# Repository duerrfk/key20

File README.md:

# What is Key 2.0?

Key 2.0 (or Key20 for short) is a Bluetooth IoT Door Lock controller. It turns a conventional electric door lock into a smart door lock that can be opened using a smartphone without the need for a physical key. Thus, Key20 is the modern version of a physical key, or, as the name suggests, the key version 2.0 for the Internet of Things (IoT) era.

Key20 consists of two parts:

1. Key20 door lock controller device, which is physically connected to the electric door lock and wirelessly via BLE to the mobile app.
2. Key20 mobile app implementing the user interface to unlock the door and communicating with the door lock controller through BLE.

```
         [ Mobile Phone w/ ]
         [    Key20 App    ]
               |
               | Bluetooth Low Energy (BLE) Connection
               |
 |---[ Key20 Door Lock Controller ]---[ Electric Door Lock ]---|
 |   [           Device           ]                            |
 |                                                             |
 |                                                             |
 |                                                             |
 |----------------------(Voltage Source)-----------------------|
                        (    12 VAC    )
```

The following image shows the Key20 door lock controller device and the Key20 app running on a smartphone.

You can get a quick impression on how Key20 works watching the following video:

[Key 2.0 Video](https://youtu.be/0vUUZOasrV8)

The main features of Key20 are:

* Using state-of-the-art security mechanisms (Elliptic Curve Diffie-Hellman Key Exchange (ECDH), HMAC) to protect against attacks. 
* Open-source software and hardware, including an open implementation of the security mechanisms. No security by obscurity! Source code for the app and door lock controller as well as Eagle files (schematic and board layout) are provided.
* Maker-friendly: using easily available cheap standard components (nRF51822 BLE chip, standard electronic parts), easy to manufacture circuit board, and open-source software and hardware design.
* Works with BLE-enabled Android 4.3 mobile devices (and of course newer versions). Porting to other mobile operating systems like iOS should be straightforward.
* Liberal licensing of software and hardware under the Apache License 2.0 and the CERN Open Hardware License 1.0, respectively.

# Security Concepts

A door lock obviously requires security mechanisms to protect from unauthorized requests to open the door. To this end, Key20 implements the following state of the art security mechanisms.

## Authorization of Door Open Requests with HMAC

All door open requests are authorized through a Keyed Hash Message Authentication Code (HMAC). A 16 byte nonce (big random number) is generated by the door lock controller for each door open request as soon as a BLE connection is made to the door lock controller. The nonce is sent to the mobile app. Both, the nonce and the shared secret, are used by the mobile app to calculate a 512 bit HMAC using the SHA-2 hashing algorithm, which is then truncated to 256 bits (HMAC512-256), and sent to the door lock controller. The door lock controller also calculates an HMAC based on the nonce and the shared secret, and only if both HMACs match, the door will be opened. 

The nonce is only valid for one door open request and effectively prevents replay attacks, i.e., an attacker sniffing on the radio channel and replaying the sniffed HMAC later. Note that the BLE radio communication is not encrypted, and it actually does not need to be encrypted since a captured HMAC is useless when re-played. 

Moreover, each nonce is only valid for 15 s to prevent man-in-the-middle attacks where an attacker intercepts the HMAC and does not forward it immediatelly but waits until the (authorized) user walks away after he is not able to open the door. Later the attacker would then send the HMAC to the door lock controller to open the door. With a time window of only 15 s (which could be reduced further), such attacks are futile since the authorized user will still be at the door.

Note that the whole authentication procedure does not include heavy-weight asymmetric crypto functions, but only light-weight hashing algorithms, which can be performed on the door lock device featuring an nRF51822 micro-controller (ARM Cortex M0) very fast in order not to delay door unlocking. 

With respect to the random nonce we would like to note the following. First, the nRF51822 chip includes a random number generator for generating random numbers from thermal noise, so nonces should be of high quality, i.e., truly random. An attack by cooling down the Bluetooth chip to reduce randomness due to thermal noise is not relevant here since this requires physical access to the lock controller installed within the building, i.e., the attacker is then already in your house.

Secondly, 128 bit nonces provide reasonable security for our purpose. Assume one door open request per millisecond (very pessimistic assumption!) and 100 years of operation, i.e., less than n = 2^42 requests to be protected. With 128 bit nonces, we have m = 2^128 possible nonce values. Then the birthday paradox can be used to calculate the probability p of at least one pair of requests sharing the same nonce, or, inversely, no nonces shared by any pair of requests. An approximation of p for n << m is p(n,m) = 1 - e^((-n^2)/(2*m)), which practically evaluates to 0 for n = 2^42 and m = 2^128. Even for n = 2^52 (one request per us; actually not possible with BLE), p(2^52,2^128) < 3e-8, which is about the probability to be hit by lightning, which is about 5.5e-8.

## Exchanging Keys with Elliptic Curve Diffie Hellman Key Exchange (ECDH)

Obviously, the critical part is the establishment of a shared secret between the door lock controller and the mobile app. Anybody in possession of the shared secret can enter the building, thus, we must ensure that only the lock controller and the Key20 app know the secret. To this end, we use Elliptic Curve Diffie-Hellman (ECDH) key exchange based on Curve 25519. We assume that the door lock controller is installed inside the building that is secured by the lock---if the attacker is already in your home, the door lock is futile anyway. Thus, only the authorized user (owner of the building) has physical access to the door lock controller. 

First, the user needs to press a button on the door lock controller device to enter key exchange mode (the red button in the pictures). Then both, the mobile app and the door lock controller calculate different key pairs based on the Elliptic Curve 25519 and exchange their public keys, which anyone can know. Using the public key of the other party and their own private keys, the lock controller and the app can calculate the same shared secret. 

Using Curve 25519 and the Curve 25519 assembler implementation optimized for ARM Cortex-M0 from the Micro NaCl project, key pairs and shared secrets can be calculated in sub-seconds on the nRF51822 BLE chip (ARM Cortex M0). 

Without further measures, DH is susceptible to man-in-the-middle attacks where an attacker actively manipulates the communication between mobile app and door lock controller. With such attacks, the attacker could exchange his own public key with both, the lock controller and the app to establish two shared secrets between him and the door lock controller, and between him and the mobile app. We prevent such attacks with the following mechanism. After key exchange, the mobile app and the door lock device both display a checksum (hash) of their version of the exchanged shared secret. The user will visually check these checksums to verify that they are the same. If they are the same, no man-in-the-middle attack has happened since the man in the middle cannot calculate the same shared secret as the door lock controller and the mobile app (after all, the private keys of door lock controller and mobile app remain private). Only then the user will confirm the key by pressing buttons on the door lock controller and the mobile app. Remember that only the authorized user has physical access to the door lock controller since it is installed within the building to be secured by the lock. 

The following image shows the mobile app and the door lock controller displaying a shared secret checksum after key exchange. The user can confirm this secret by pushing the green button the the lock controller device and the Confirm Key button of the app.

## Why not Standard Bluetooth Security?

Actually, Bluetooth 4.2 implements security concepts similar to the mechanisms described above. So it is a valid question why don't we just rely on the security concepts implemented by Bluetooth?

A good overview why Bluetooth might not be as secure as we would like it to be is provided by [Francisco Corella](https://pomcor.com/2015/06/03/has-bluetooth-become-secure/). So we refer the interested reader to his page for the technical details and a discussion of Bluetooth security. We also would like to add that many mobile devices still do not implement Bluetooth 4.2 but only Bluetooth 4.0, which is even less secure than Bluetooth 4.2.

So we decided not to rely on Bluetooth security mechanisms, but rather implement all security protocols on the application layer using state of the art security mechanisms as described above.

# Bluetooth Door Lock Controller Device

The Door Lock Controller Device needs to be connected to the electric door lock (2 cables). You can simply replace a manual switch by the door lock controller device. 

The door lock controller needs to be placed in Bluetooth radio range to the door and inside the building. Typical radio ranges are about 10 m. Depending on the walls, the distance might be shorter or longer. In our experience, one concrete wall is no problem, but two might block the radio signal.  

## Door Lock Controller Hardware

The door lock controller hardware is designed for operating AC (alternating current) electric door locks, which typically run from 6-12 VAC. 

The hardware design (schematics and board layout for Eagle) for the door lock controller device can be found in folder `pcb/key20-ble`. 

The following images show the hardware and schematic. The hardware basically concists of one circuit board (PCB). We deliberately used a simple single-sided through-hole design to help makers producing their own boards. An LCD, a power switch, and two push buttons for user interaction are connected to the main PCB. An ob-board voltage regulator provides 3.3 V fed by an external DC power supply (anything between 4 V and 30 V will work). The circuit draws less than 50 mA when the lock is operated, thus, you can use a cheap 5.0 V USB power supply. With a little modification, we could also switch off the LCD when not needed, and the device could run from 4 AA-size batteries most probably for years.

The main part of the hardware is an nRF51822 BLE chip from Nordic Semiconductors. You can buy so-called "Bluetooth 4.0" breakout boards with an nRF51822 (version 3, variant AA w/ 16 kB of RAM and 256 kB flash memory) and two 2x9 connectors (2 mm pitch) for about 6 US$ including shipping. To connect the Bluetooth 4.0 board hosting the nRF51822, the PCB has two 2x9 pin connectors (no SMD soldering required). The nRF51822 features an ARM Cortex M0 micro-controller and a so-called softdevice implementing the Bluetooth stack, which runs together with the application logic on the ARM Cortex M0 processor. Key20 uses the S110 softdevice version 8.0 (see next sub-section on how to flash the softdevice and the Key20 application code). 

The nRF51822 operates the electric door lock through a TRIAC. Note that most electric door locks use alternating current (AC), so a transistor will not work. We have added a snubber circuit (capacitor and resistor) to drive the inductive load (electric door lock) since TRIACs are sensitive to sudden voltage jumps possibly leading to unwanted turn-on, i.e., door unlocking. The TRIAC is operated in quadrant 2 and 3 (current flowing out of the gate) to avoid the less sensitive quadrant 4. Since the TRIAC needs about 30 mA to trigger reliably, a transistor is used to drive the TRIAC by the nRF51822, reducing the current on the micro-controller's GPIO to less than 1 mA.

Note that our design is targeting electric door locks using small AC voltages (typically 6-12 V AC). Theoretically, the TRIAC can drive 230 V loads up to 16 A. However, for safe 230 V and higer current operation the design has to be adapted, e.g., X2 snubber capacitor, isolation of the low-voltage part (3.3 V microcontroller) from the 230 V part through an opto-TRIAC, larger trace width and distances, etc. 

An LCD is used to implement the secure key exchange procedure described above (visual key verification to avoid man-in-the-middle attacks). We used a common HD44780-compatible LCD display with 2x16 characters (1602A, 2-3 US$ including shipping). The LCD is connected to the main PCB through a ribbon cable. We designed a custom adapter board for connecting and mounting the 1602A LCD (see folder `pcb/lcd1602a-connector`).

## Lock Controller Software

### Overview

The software for the door lock controller can be found in folder `nrf51`.

Keys (shared secrets) are persistently stored in flash. Currently, we store 4 keys, but you can easily increase this number up to the limit of the flash size (nRF51822 version 3, variant AA comes with 256 kB flash, and each key consumes only 32 bytes).  

Application events and a state machine approach are used to implement the application logic. Events are handled outside the interrupt context to avoid blocking the softdevice. In particular, actions like calculating keys or hashes can take significant time, although the crypto implementations used by Key20 can also process such compute-heavy tasks in just hundreds of milliseconds.   

A lean-and-mean library was implemented for the nRF51822 chip to drive the LCD. 

For more details, please have a look at the source code.

### Prerequisites for Building the Software

No heavy-weight IDE is required to build the code. However, still a few tools are required to build and flash the code (tested with the given version numbers):

* [nRF51 SDK, version 10.0.0](http://developer.nordicsemi.com/nRF5_SDK/)
* [nRF5x Command Line Tools, version 8.2.0](https://www.nordicsemi.com/eng/Products/nRF51-DK)
* [Softdevice S110, version 8.0.0](https://www.nordicsemi.com/eng/Products/nRF51-DK)
* Flashing and debugging hardware, e.g., [Segger J-Link EDU](https://www.segger.com/j-link-edu.html) (about 50 US$, only for non-commerical use!). The nRF51 Developers Kit (DK) comes with an on-board Segger programmer, but for flashing the Key20 board, you need an external programmer like the J-Link EDU. 
* [Tool chain (compiler, linker, etc.) for ARM](https://launchpad.net/gcc-arm-embedded/+download)

### Building and Flashing the Software

First, adapt the Makefile by defining the following variables:

* `NRF51_SDK`: path to the nRF51 SDK directory
* `CROSS`: path to the compiler tools
* `CFLAGS`: add `-DTARGET_BOARD_NRF51DK` if you compile for the nRF51 Development Kit (DK); if this definition is not set, you compile for the Key20 board.
* `LINKER_SCRIPT`: set to `nrf51422_ac_s110.ld` for the nRF51 DK (nRF51422, variant AC) or to `nrf51822_aa_s110.ld` for the Key20 board (nRF51822, variant AA).

Compiling the code:

```
$ cd nrf51
$ make
```

Flashing the softdevice:

```
$ nrfjprog --family NRF51 --program s110_nrf51_8.0.0_softdevice.hex --chiperase --verify
```

Flashing the application:

```
nrfjprog --family NRF51 --program key20.hex --verify --sectorerase
```

Rebooting after flashing:

```
nrfjprog -r
```

# Android App

The source code of the Key20 app for Android can be found in folder `android/Key20`. The code was developed with Android Studio 2.1.

The app requires a BLE-enabled mobile device running Android version 4.3 "Jelly Bean" (API level 18) or higher. 

The following images show the two major tabs of the app: one for opening the door, and the second for exchanging keys between the app and the door lock controller.

# License and Acknowledgments

The Key20 software (contents of folders `nrf51` and `android`) is licensed under the Apache License, Version 2.0.

The Key20 hardware documentation (contents of folder `pcb`) is licensed under the CERN Open Hardware Licence, Version 1.2

Both licenses are included in the repository in the files `LICENSE-SOFTWARE` and `LICENSE-HARDWARE`, respectively.

Key20 uses the Micro-NaCl crypto library, specifically, AVRNaCl (folder `avrnacl`) by Michael Hutter and Peter Schwabe, and M0NaCl  (folder `curve25519-cortexm0`) by Björn Haase and Ana Helena Sánchez. The authors have released Micro-NaCl to the public domain, and we gratefully acknowledge their generous contribution.

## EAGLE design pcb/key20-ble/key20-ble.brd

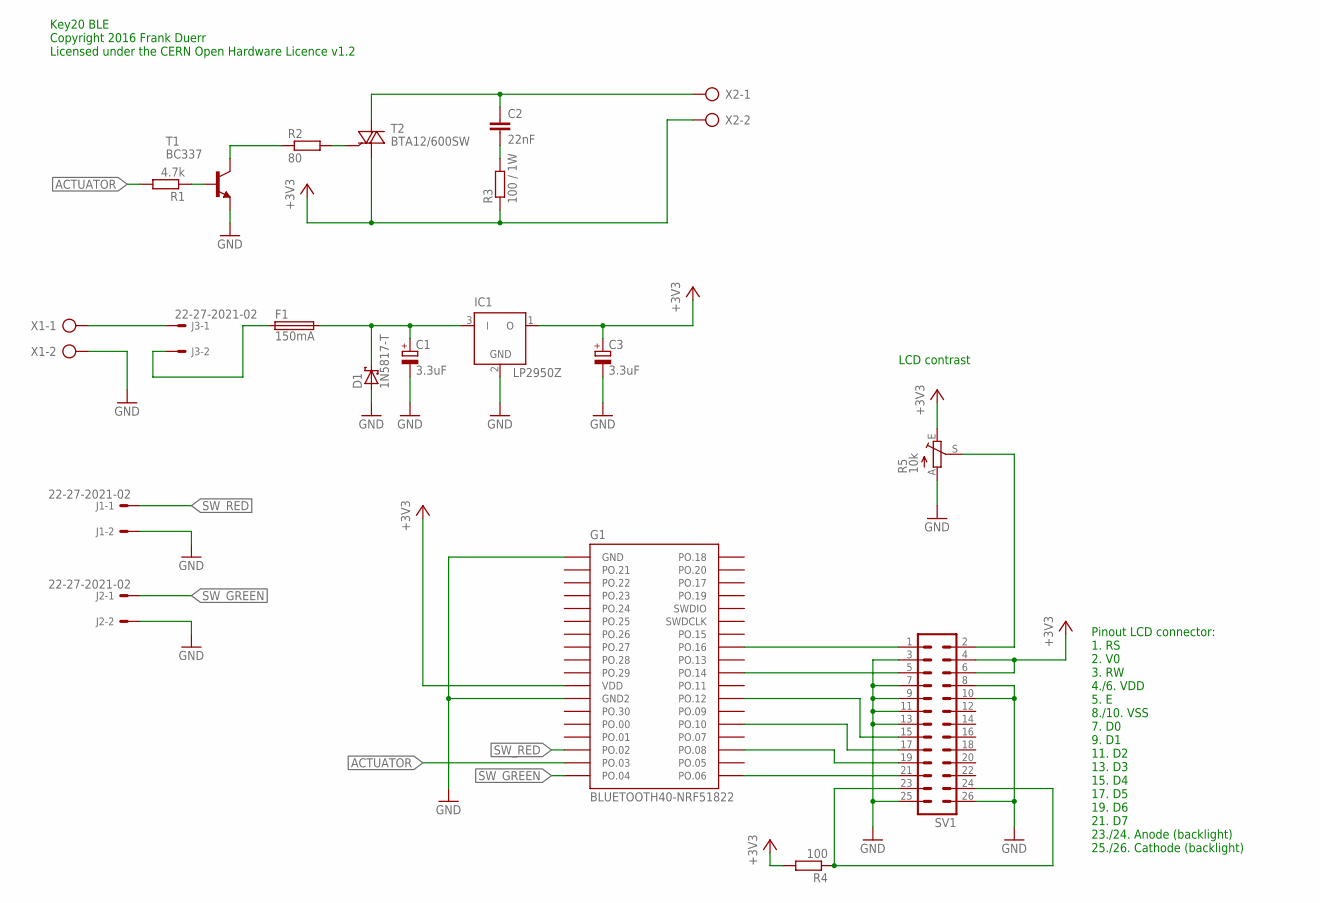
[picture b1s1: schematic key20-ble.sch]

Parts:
C1, C3: 3.3uF; E2,5-5
C2: 22nF; C102-054X133
D1: 1N5817-T; DO41-7.6
F1: 150mA; SH22,5
G1: BLUETOOTH40-NRF51822; BLUETOOTH40-NR51822
IC1: LP2950Z; TO92
J1, J2, J3: 22-27-2021-02; 6410-02
R1: 4.7k; 0207/7
R2: 80; 0207/7
R3: 100 / 1W; 0207/7
R4: 100; 0207/7
R5: 10k; CA6V
SV1: ML26
T1: BC337; TO92
T2: BTA12/600SW; TO220BV
X1, X2: AK500/2

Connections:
+3V3: C3.+, G1.VDD, IC1.1 (O), R3.1, R4.2, R5.E, SV1.4, SV1.6, T2.T1 (A1), X2.2
ACTUATOR: G1.PO.03, R1.2
GND: C1.-, C3.-, D1.A, G1.GND, G1.GND2, IC1.2 (GND), J1.2, J2.2, R5.A, SV1.3, SV1.7, SV1.8, SV1.9, SV1.10, SV1.11, SV1.13, SV1.25, SV1.26, T1.1 (E), X1.2
unnamed: R2.2, T2.G
unnamed: C2.2, R3.2
unnamed: C2.1, T2.T2 (A2), X2.1
unnamed: R1.1, T1.2 (B)
unnamed: R2.1, T1.3 (C)
unnamed: G1.PO.08, SV1.19
unnamed: F1.1, J3.2
unnamed: G1.PO.06, SV1.21
unnamed: G1.PO.14, SV1.5
unnamed: G1.PO.16, SV1.1
unnamed: R5.S, SV1.2
unnamed: R4.1, SV1.23, SV1.24
unnamed: J3.1, X1.1
unnamed: C1.+, D1.C, F1.2, IC1.3 (I)
unnamed: G1.PO.10, SV1.17
unnamed: G1.PO.12, SV1.15
SW_GREEN: G1.PO.04, J2.1
SW_RED: G1.PO.02, J1.1

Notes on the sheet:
Pinout LCD connector: 1. RS 2. V0 3. RW 4./6. VDD 5. E 8./10. VSS 7. D0 9. D1 11. D2 13. D3 15. D4 17. D5 19. D6 21. D7 23./24. Anode (backlight) 25./26. Cathode (backlight)
LCD contrast
Key20 BLE Copyright 2016 Frank Duerr Licensed under the CERN Open Hardware Licence v1.2

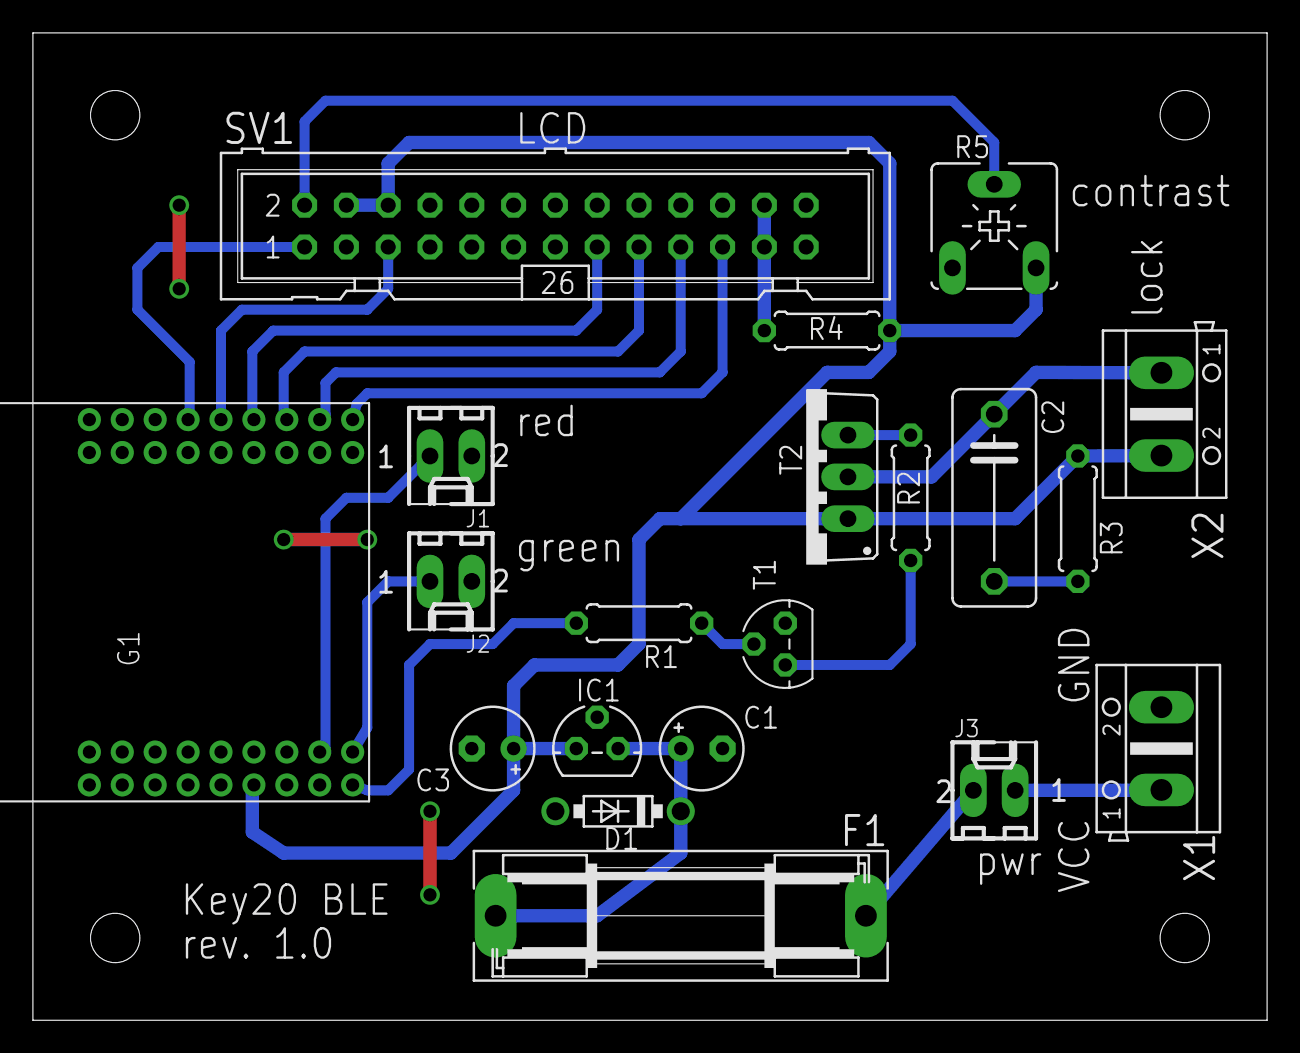
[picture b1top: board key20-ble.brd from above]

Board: 2 copper layers, 75.0 x 60.0 mm, 20 parts (0 on the bottom side), 21 nets.

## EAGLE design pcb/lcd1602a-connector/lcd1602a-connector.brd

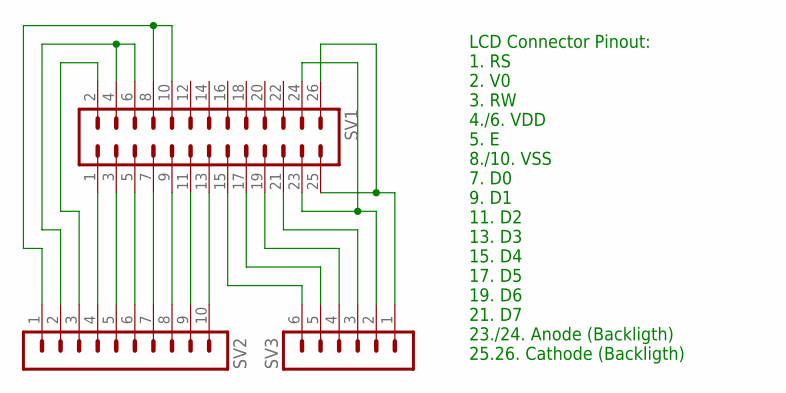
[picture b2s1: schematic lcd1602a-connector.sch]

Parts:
SV1: ML26
SV2: MA10-1
SV3: MA06-1

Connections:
unnamed: SV1.1, SV2.4
unnamed: SV1.3, SV2.5
unnamed: SV1.5, SV2.6
unnamed: SV1.7, SV2.7
unnamed: SV1.9, SV2.8
unnamed: SV1.11, SV2.9
unnamed: SV1.13, SV2.10
unnamed: SV1.15, SV3.6
unnamed: SV1.17, SV3.5
unnamed: SV1.21, SV3.3
unnamed: SV1.23, SV1.24, SV3.2
unnamed: SV1.19, SV3.4
unnamed: SV1.25, SV1.26, SV3.1
unnamed: SV1.2, SV2.3
unnamed: SV1.4, SV1.6, SV2.2
unnamed: SV1.8, SV1.10, SV2.1

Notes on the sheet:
LCD Connector Pinout: 1. RS 2. V0 3. RW 4./6. VDD 5. E 8./10. VSS 7. D0 9. D1 11. D2 13. D3 15. D4 17. D5 19. D6 21. D7 23./24. Anode (Backligth) 25.26. Cathode (Backligth)

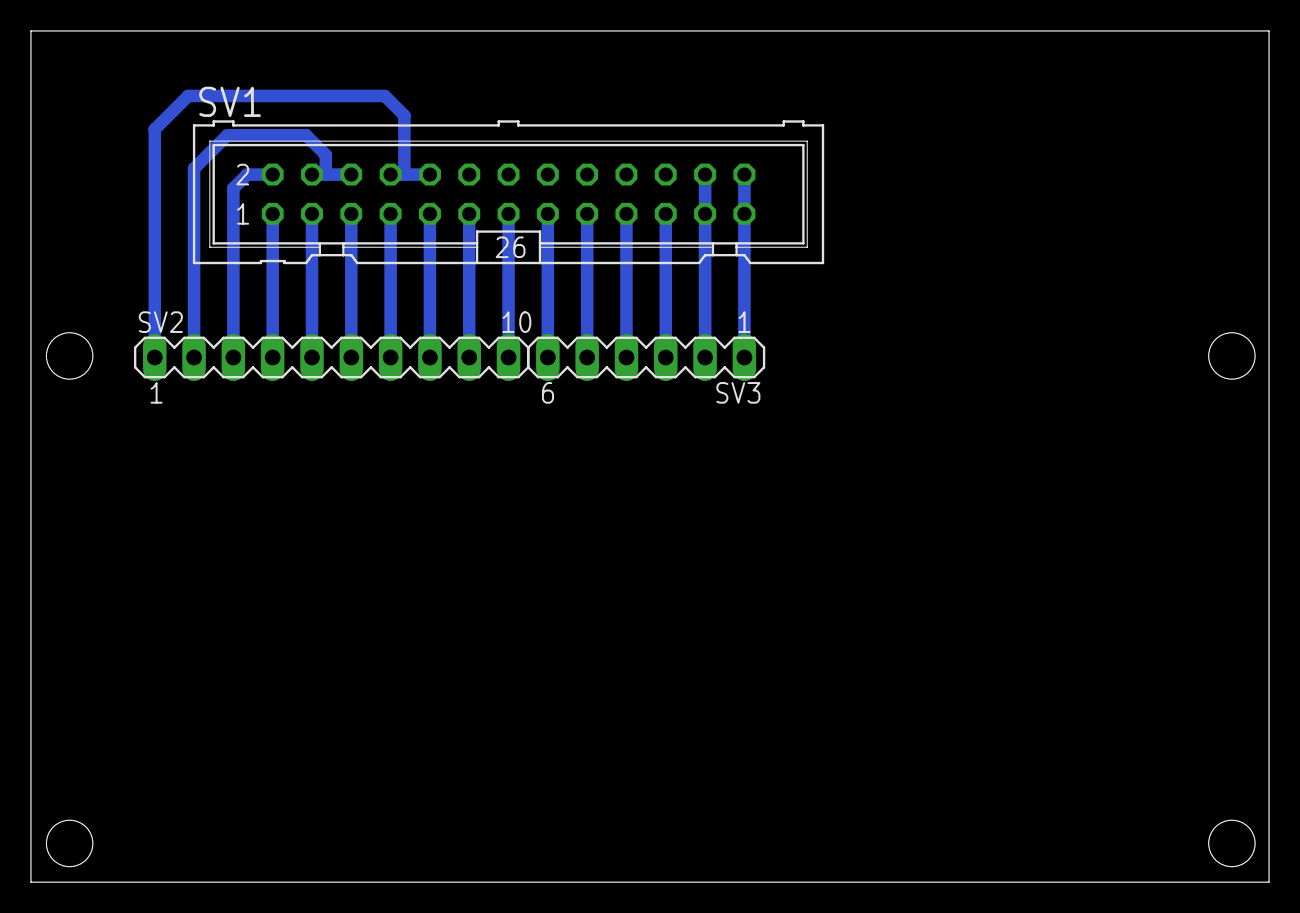
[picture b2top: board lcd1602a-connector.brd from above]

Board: 2 copper layers, 80.0 x 55.0 mm, 3 parts (0 on the bottom side), 16 nets.

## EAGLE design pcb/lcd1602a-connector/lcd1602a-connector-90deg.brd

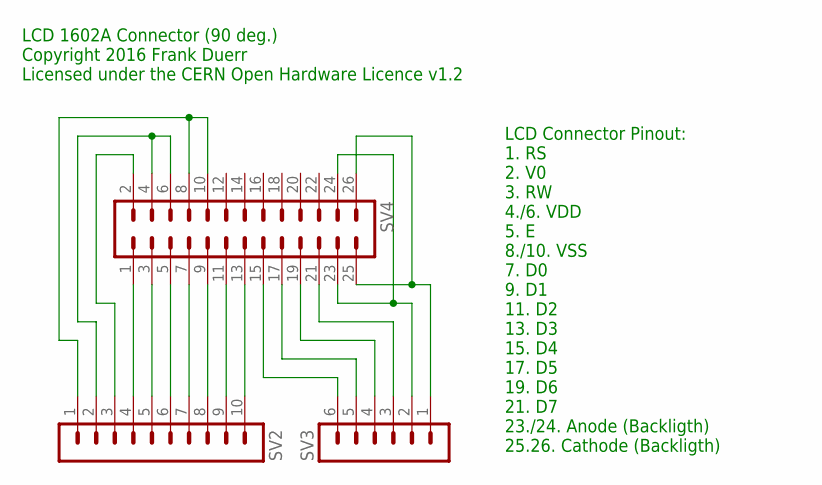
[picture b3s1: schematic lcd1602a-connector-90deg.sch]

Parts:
SV2: MA10-1
SV3: MA06-1
SV4: ML26L

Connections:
unnamed: SV2.4, SV4.1
unnamed: SV2.5, SV4.3
unnamed: SV2.6, SV4.5
unnamed: SV2.7, SV4.7
unnamed: SV2.8, SV4.9
unnamed: SV2.9, SV4.11
unnamed: SV2.10, SV4.13
unnamed: SV3.6, SV4.15
unnamed: SV3.5, SV4.17
unnamed: SV3.3, SV4.21
unnamed: SV3.2, SV4.23, SV4.24
unnamed: SV3.4, SV4.19
unnamed: SV3.1, SV4.25, SV4.26
unnamed: SV2.3, SV4.2
unnamed: SV2.2, SV4.4, SV4.6
unnamed: SV2.1, SV4.8, SV4.10

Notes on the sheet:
LCD Connector Pinout: 1. RS 2. V0 3. RW 4./6. VDD 5. E 8./10. VSS 7. D0 9. D1 11. D2 13. D3 15. D4 17. D5 19. D6 21. D7 23./24. Anode (Backligth) 25.26. Cathode (Backligth)
LCD 1602A Connector (90 deg.) Copyright 2016 Frank Duerr Licensed under the CERN Open Hardware Licence v1.2

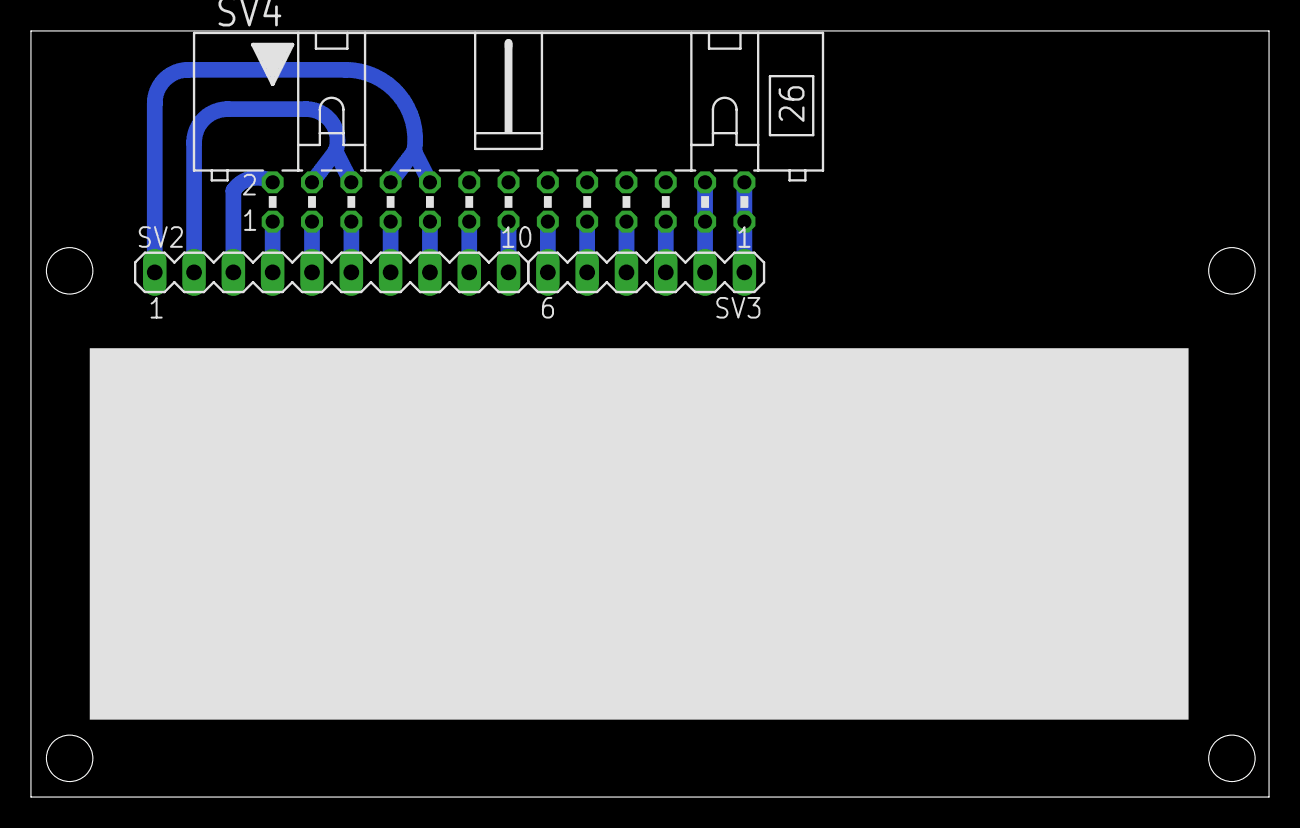
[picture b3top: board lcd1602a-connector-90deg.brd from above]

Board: 2 copper layers, 80.0 x 49.5 mm, 3 parts (0 on the bottom side), 16 nets.

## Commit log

2016-09-28 Initial check-in
2016-10-03 Renamed startup file and adapted Makefile.
2016-10-03 Adapted Makefile and code to easily switch between compiling for nRF51 DK and Key20 board.
2016-10-03 Fixed small mistake in readme file.
2016-10-04 Protect critical sections of application event queue.
2016-10-04 Removed unnecessary .map file.
2016-10-23 Fixed problem when connecting to BLE device after re-enabling Bluetooth adapter
2016-11-01 Added big picture to README.
2017-06-10 Fixed bug in key exchange (device not sending correct key number in second part of DH key)
2017-06-10 Fixed bug: key number not loaded for keys with numbers greater 1

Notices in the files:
README.md:
License and Acknowledgments:
The Key20 software (contents of folders `nrf51` and `android`) is licensed under the Apache License, Version 2.0.
The Key20 hardware documentation (contents of folder `pcb`) is licensed under the CERN Open Hardware Licence, Version 1.2
Both licenses are included in the repository in the files `LICENSE-SOFTWARE` and `LICENSE-HARDWARE`, respectively.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
The authors have released Micro-NaCl to the public domain, and we gratefully acknowledge their generous contribution.
